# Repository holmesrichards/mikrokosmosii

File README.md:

# Mikrokosmos II

This is a synth module in Kosmo format, inspired by Music Thing Modular's [Mikrophonie](https://www.musicthing.co.uk/Mikrophonie/). Like that module, Mikrokosmos II has a piezo pickup attached behind the front panel, and the circuit amplifies the piezo signal and sends it to the output. There is a tactile scratch area on the front panel. You can use your fingernail or a guitar pick to scrape across it and generate output. It will also pick up sounds when you tap or thump on the synth case, plug or unplug cables, and so on. People have attached springs to the front panel, even a coil spring type doorstop. There are lots of possibilities.

There also is a jack for plugging in an external piezo pickup attached to a cable.

The first version of Mikrokosmos was a Kosmo conversion of the Mikrophonie circuit. Mikrokosmos II replaces that circuit with one based on a [design](https://www.logosfoundation.org/g_texts/Orfeus/preamps/piezo_disks.html) by composer, performer, and instrument maker Godfried-Willem Raes. This preamp is designed specifically for piezo pickups and gives better frequency response than a typical constant impedance amplifier.

## About the name

Mikrophonie's name comes from that of a [composition](https://en.wikipedia.org/wiki/Mikrophonie_(Stockhausen)) by Karlheinz Stockhausen. "Mikrokosmos" is an obvious portmanteau of "Mikrophonie" and "Kosmo", and pays homage to a [collection of piano pieces](https://en.wikipedia.org/wiki/Mikrokosmos_(Bart%C3%B3k)) with that name by Béla Bartók. Apparently it also is the name of a song by BTS, but that has nothing to do with this module.

## Current draw
? mA +12 V, ? mA -12 V

## Photos

## Documentation

* [Schematic](Docs/mikrokosmos-ii.pdf)
* PCB layout: [front](Docs/mikrokosmos-ii_layout_front.pdf), [back](Docs/mikrokosmos-ii_layout_back.pdf)
* [BOM](Docs/mikrokosmos-ii_bom.md)
* [Build notes](Docs/build.md)

## GitHub repository

* [https://github.com/holmesrichards/mikrokosmosii](https://github.com/holmesrichards/mikrokosmosii)

## Submodules

This repo uses submodules aoKicad and Kosmo_panel, which provide needed libaries for KiCad. To clone:

```
git clone git@github.com:holmesrichards/microkosmos-ii.git
git submodule init
git submodule update
```

Alternatively do

```
git clone --recurse-submodules git@github.com:holmesrichards/microkosmos-ii.git
```

Or if you download the repository as a zip file, you must also click on the "aoKicad" and "Kosmo\_panel" links on the GitHub page (they'll have "@ something" after them) and download them as separate zip files which you can unzip into this repo's aoKicad and Kosmo\_panel directories.

If desired, copy the files from aoKicad and Kosmo\_panel to wherever you prefer (your KiCad user library directory, for instance, if you have one). Then in KiCad, go into Edit Symbols and add symbol libraries 

```
aoKicad/ao_symbols
Kosmo_panel/Kosmo
```
and go into Edit Footprints and add footprint libraries 
```
aoKicad/ao_tht
Kosmo_panel/Kosmo_panel.
```

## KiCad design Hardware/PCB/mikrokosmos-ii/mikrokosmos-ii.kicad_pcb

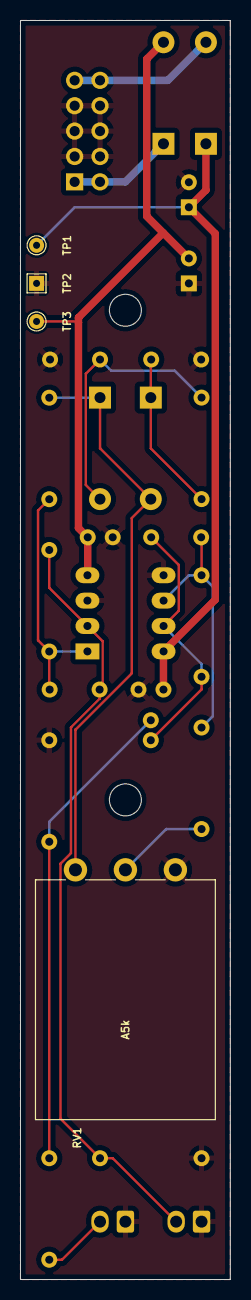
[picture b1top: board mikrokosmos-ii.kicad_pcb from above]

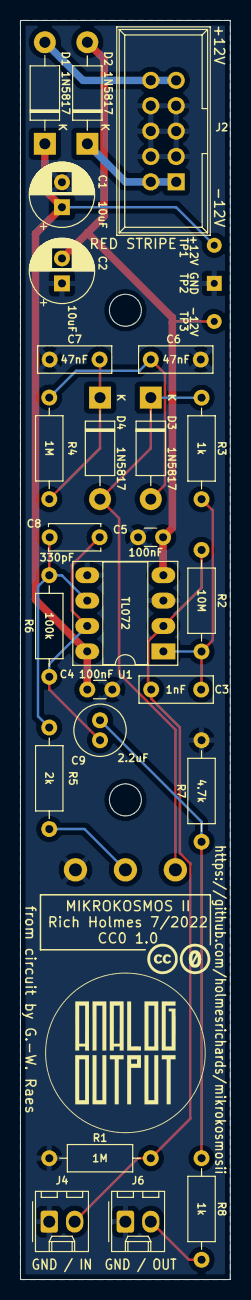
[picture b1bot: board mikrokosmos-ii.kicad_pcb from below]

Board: 2 copper layers, 21.0 x 126.0 mm, 34 parts (27 on the bottom side), 15 nets.

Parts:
C1, C2: 10uF; CP_Radial_D6.3mm_P2.50mm
C3: 1nF; C_Rect_L7.2mm_W2.5mm_P5.00mm_FKS2_FKP2_MKS2_MKP2
C4, C5: 100nF; C_Disc_D3.0mm_W1.6mm_P2.50mm
C6, C7: 47nF; C_Rect_L7.2mm_W2.5mm_P5.00mm_FKS2_FKP2_MKS2_MKP2
C8: 330pF; C_Disc_D5.0mm_W2.5mm_P5.00mm
C9: 2.2uF; C_Radial_D5.0mm_H11.0mm_P2.00mm
D1, D2, D3, D4: 1N5817; D_DO-41_SOD81_P10.16mm_Horizontal
GRAF1: Graphic; mikrokosmos-ii_panel_holes
GRAF2: CC0 logo; CC0_logo
GRAF3: AO logo; analogoutput
H1, H2: MountingHole; MountingHole_3.2mm_M3
J2: Synth_power_2x5; Power_Header
J4, J6: 2_pin_Molex_header; Molex_KK-254_AE-6410-02A_1x02_P2.54mm_Vertical
R1, R4: 1M; R_Axial_DIN0207_L6.3mm_D2.5mm_P10.16mm_Horizontal
R2: 10M; R_Axial_DIN0207_L6.3mm_D2.5mm_P10.16mm_Horizontal
R3, R8: 1k; R_Axial_DIN0207_L6.3mm_D2.5mm_P10.16mm_Horizontal
R5: 2k; R_Axial_DIN0207_L6.3mm_D2.5mm_P10.16mm_Horizontal
R6: 100k; R_Axial_DIN0207_L6.3mm_D2.5mm_P10.16mm_Horizontal
R7: 4.7k; R_Axial_DIN0207_L6.3mm_D2.5mm_P10.16mm_Horizontal
RV1: A5k; Potentiometer_Alpha_16mm_Single_Vertical
TP1: +12V; TestPoint_THTPad_D1.5mm_Drill0.7mm
TP2: GND; TestPoint_THTPad_1.5x1.5mm_Drill0.7mm
TP3: -12V; TestPoint_THTPad_D1.5mm_Drill0.7mm
U1: TL072; DIP-8_W7.62mm_Socket_LongPads

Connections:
+12V: C1.1, C4.1, D1.1 (K), TP1.1, U1.8 (V+)
-12V: C2.2, C5.2, D2.2 (A), TP3.1, U1.4 (V-)
/+12V_INLET: D1.2 (A), J2.9 (+12V), J2.10 (+12V)
/-12V_INLET: D2.1 (K), J2.1 (-12V), J2.2 (-12V)
/PIEZO_IN: C3.2, J4.2, R1.1, R2.2, U1.2 (-)
/PREAMP_OUT: J6.2, R8.1
GND: C1.2, C2.1, C4.2, C5.1, C6.2, C7.2, J2.3 (GND), J2.4 (GND), J2.5 (GND), J2.6 (GND), J2.7 (GND), J2.8 (GND), J4.1, J6.1, R1.2, R7.2, RV1.1, TP2.1, U1.3 (+), U1.5 (+)
unnamed: C3.1, R2.1, R3.2, U1.1
unnamed: C6.1, D3.2 (A), R4.2
unnamed: C7.1, D4.1 (K), R4.1
unnamed: C8.1, C9.1, R6.1, U1.7
unnamed: C8.2, R5.1, R6.2, U1.6 (-)
unnamed: C9.2, R7.1, R8.2
unnamed: D3.1 (K), D4.2 (A), R3.1, RV1.3
unnamed: R5.2, RV1.2

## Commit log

2022-06-10 Initial version
2022-06-11 README, reorient capacitor
2022-06-20 Small refinements to layout and schem
2022-07-08 Vendors
2022-07-09 PCB touchup, reorg files, panel
2022-07-09 panel svg update
2022-08-19 panel, PCB updates
2022-09-23 Pre fab tweaks, Gerbers, cap descriptions
2022-10-11 Documentation
2022-10-11 License
2022-10-11 README update
2022-10-12 build notes and BOM update
2022-10-12 build notes and BOM correction
2022-10-12 Link fix
